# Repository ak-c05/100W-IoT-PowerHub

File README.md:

# 100W IoT Power Hub | ESP32-C3

A custom-engineered, dual-rail Power Delivery (PD) hub featuring hardware-level I2C telemetry, commercial DFM clamshell mechanics, and an asynchronous WebSocket control dashboard. 

---

## Mechanical Engineering (DFM)

The enclosure is architected for a friction-fit prototyping phase, scaling to ultrasonic welding for mass production.
* **Non-Collision Assembly:** Designed with strict vertical U-channels for all I/O ports, eliminating plastic undercuts and allowing seamless top-down Z-axis assembly.
* **Interference Tolerancing:** Utilizes a modeled `0.05mm` press-pull lip-and-groove parting line to achieve a reliable friction fit without failure-prone snap hooks.
* **Kinematic Trapping:** The PCB is cradled by lower bosses and secured by mirrored upper retaining posts featuring a `0.2mm` rattle gap to guarantee closure without crushing the FR4 fiberglass.
* **Captive Actuation:** Features a custom 15mm "long-stem mushroom" plunger mechanism with strict 0.2mm clearance tolerances for the tactile UI switch.

---

## Electrical Architecture

Designed in KiCad 7/8, the motherboard isolates high-power delivery protocols from sensitive RF and logic components.
* **Dual-Rail Telemetry:** Utilizes two Texas Instruments INA219 ICs (I2C) for independent, high-speed monitoring of both the 12V Main and 9V PD lines.
* **Hardware PD Negotiation:** Integrates the autonomous SW3516 buck-boost controller for dedicated Type-C PD 3.0 protocol handshakes, offloading thermal and negotiation logic from the MCU.
* **RF Isolation:** Antenna routing and component placement are optimized to prevent the ESP32-C3's 2.4GHz radio from introducing jitter into the analog-to-digital current sensing pathways.

---

## Embedded Firmware & IoT

The C++ backend operates on a strict, non-blocking deterministic state machine, ensuring network handling never interrupts safety-critical hardware isolation.
* **Asynchronous WebSockets:** The ESP32 hosts a continuous WebSocket tunnel, pushing serialized JSON packets to the frontend only when clients are actively connected, saving CPU cycles.
* **PROGMEM Decoupling:** All HTML, CSS, and JavaScript assets are decoupled into an external `dashboard.h` file and stored in flash memory, preserving SRAM for runtime telemetry.
* **Hardware-Agnostic Graphics:** Drives a 1.3" SH1106 OLED using the U8g2 memory buffer, pushing mathematical frame geometry in single I2C blasts to prevent screen tearing.
* **Zero-Blocking Safety:** The 20-millisecond overcurrent protection polling loop runs independently of the network stack; physical hardware isolation always overrides remote UI commands.

---

## Future Roadmap
* Implementation of `WiFiManager` (Captive Portal) for dynamic AP provisioning, removing hardcoded network credentials from the master branch.

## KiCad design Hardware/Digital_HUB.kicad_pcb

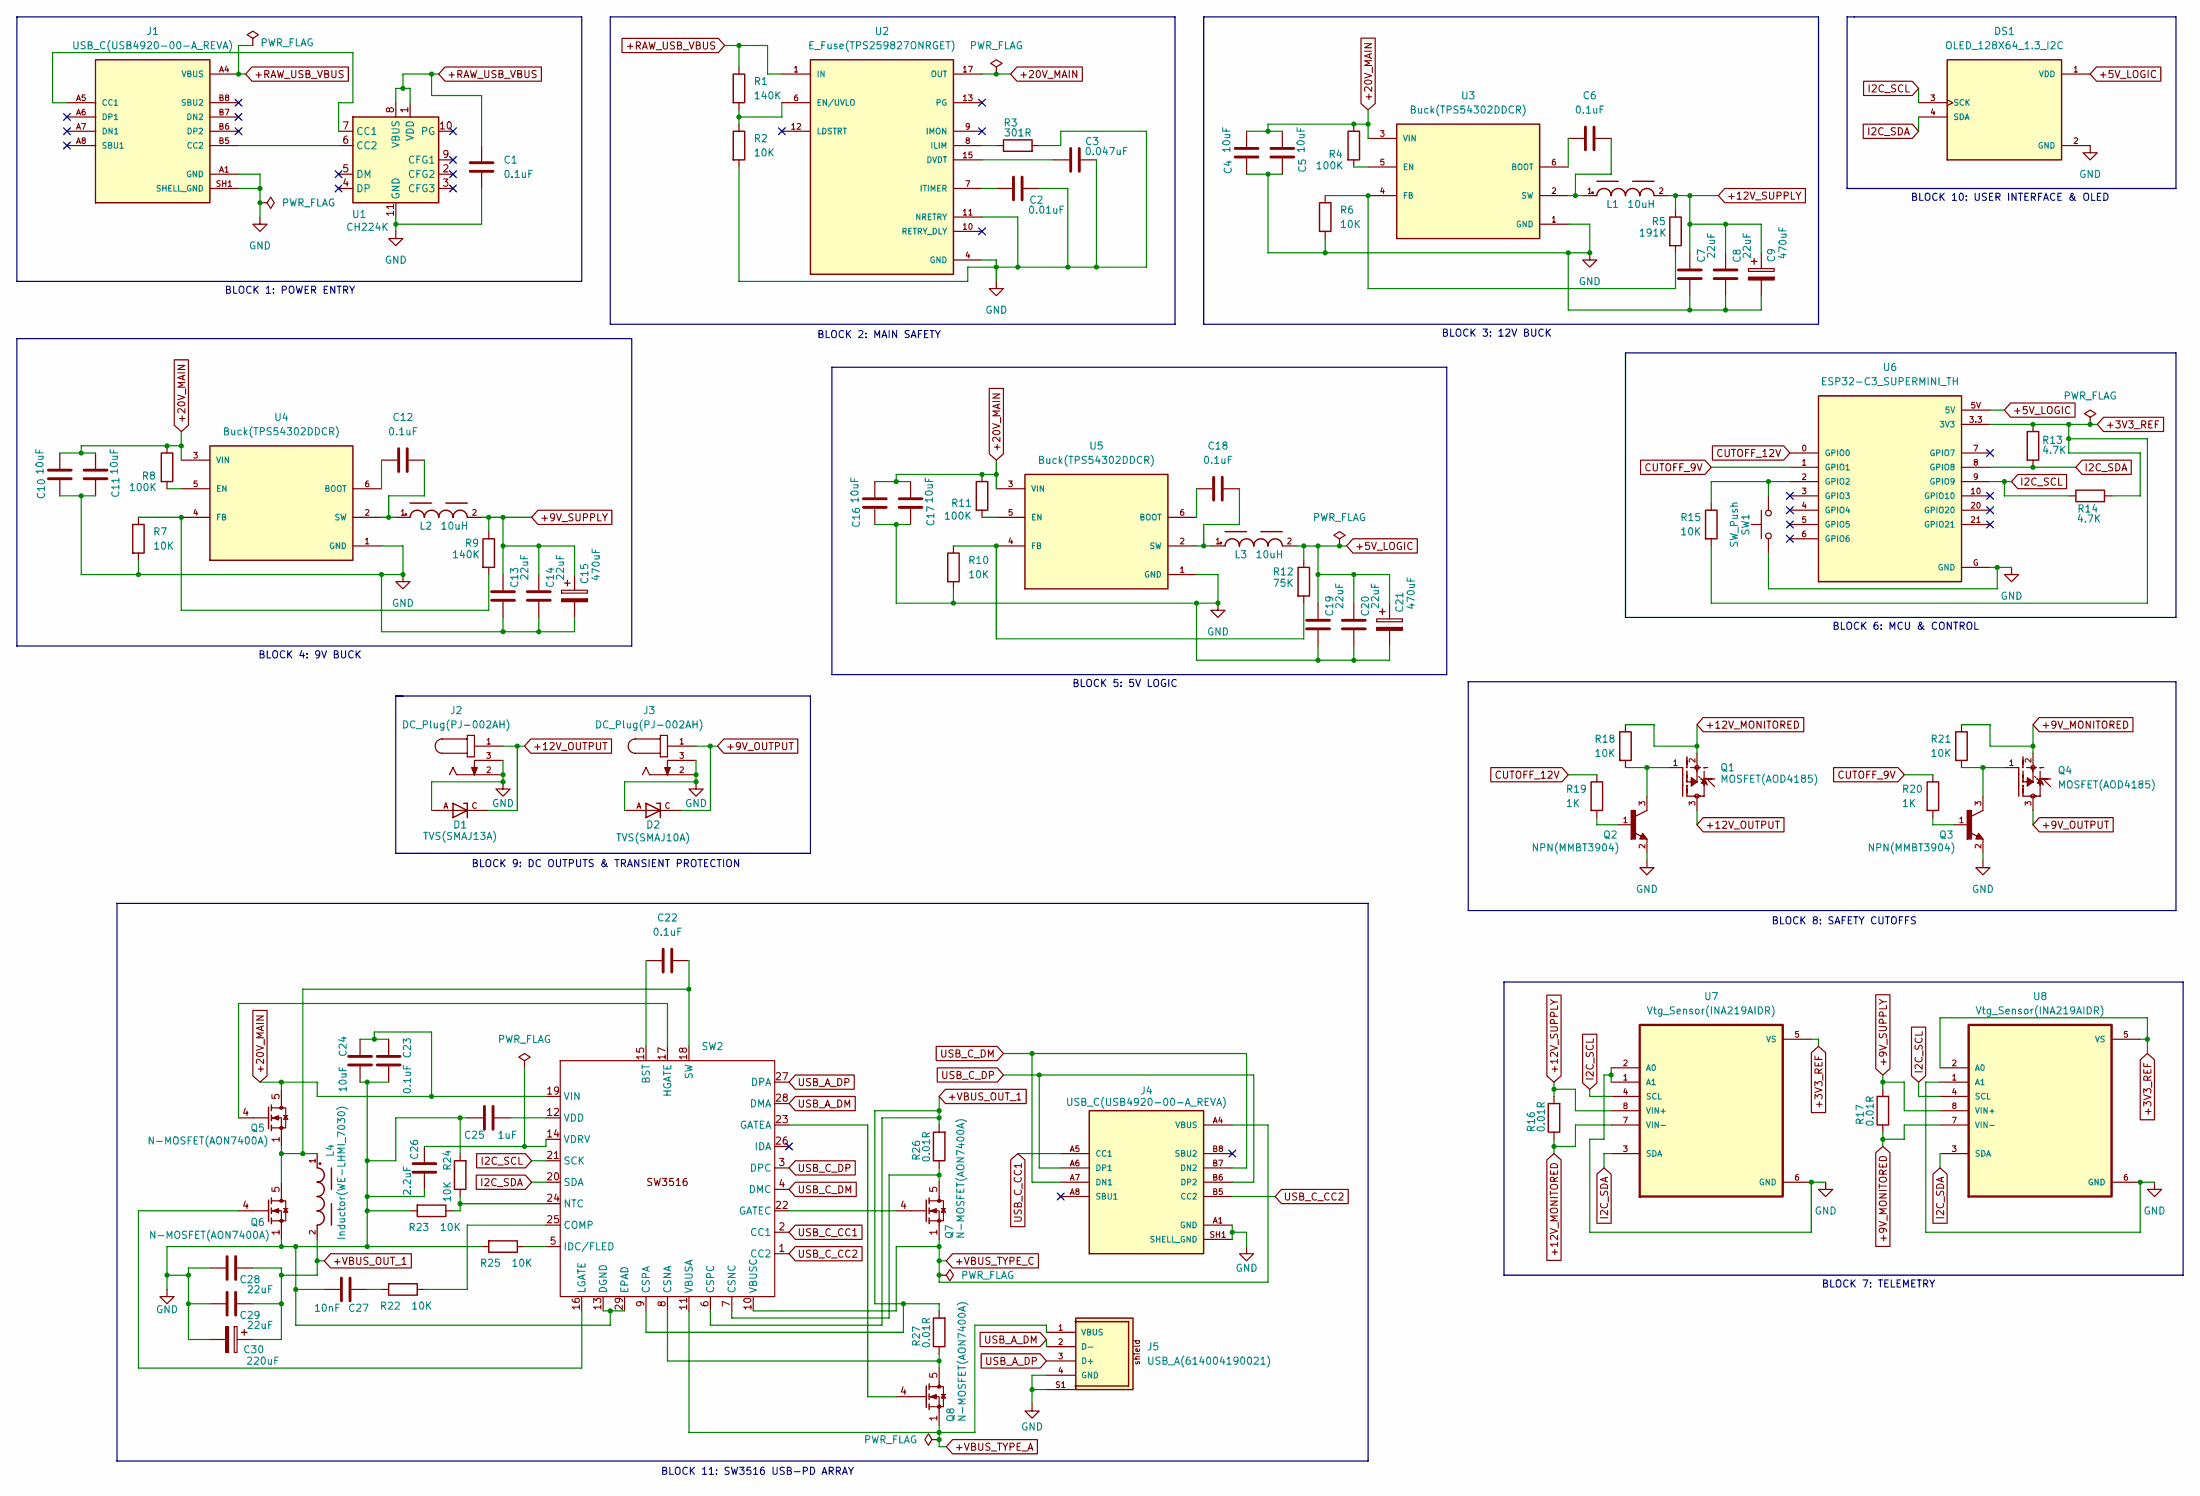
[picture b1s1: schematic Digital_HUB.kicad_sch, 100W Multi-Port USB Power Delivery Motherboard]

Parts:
C1, C6, C12, C18, C22, C23: 0.1uF; C_0603_1608Metric
C2: 0.01uF; C_0603_1608Metric
C3: 0.047uF; C_0603_1608Metric
C4, C5, C10, C11, C16, C17, C24: 10uF; C_0603_1608Metric
C7, C8, C13, C14, C19, C20, C28, C29: 22uF; C_0603_1608Metric
C9, C15, C21: 470uF; CP_Elec_10x10.5
C25: 1uF; C_0603_1608Metric
C26: 2.2uF; C_0603_1608Metric
C27: 10nF; C_0603_1608Metric
C30: 220uF; CP_Elec_10x10.5
D1: TVS(SMAJ13A); TVS13(DIOM4325X250N); PARTREV S2102
D2: TVS(SMAJ10A); TVS10(DIOM4325X250N); PARTREV S2102
DS1: OLED_128X64_1.3_I2C; LCD_OLED_128X64_1.3_I2C; PARTREV NA
J1, J4: USB_C(USB4920-00-A_REVA); USB_C(GCT_USB4920-00-A_REVA); PARTREV A
J2, J3: DC_Plug(PJ-002AH); DC_Plug(CUI_PJ-002AH)
J5: USB_A(614004190021)
L1, L2, L3: 10uH; Inductor(WE-LHMI_7030)
L4: Inductor(WE-LHMI_7030)
Q1, Q4: MOSFET(AOD4185)
Q2, Q3: NPN(MMBT3904); PARTREV 2025-06-30
Q5, Q6, Q7, Q8: N-MOSFET(AON7400A); TRANS_AON7407
R1, R9: 140K; R_0603_1608Metric
R2, R6, R7, R10, R15, R18, R21, R22, R23, R24, R25: 10K; R_0603_1608Metric
R3: 301R; R_0603_1608Metric
R4, R8, R11: 100K; R_0603_1608Metric
R5: 191K; R_0603_1608Metric
R12: 75K; R_0603_1608Metric
R13, R14: 4.7K; R_0603_1608Metric
R16, R17, R26, R27: 0.01R; R_2512_6332Metric
R19, R20: 1K; R_0603_1608Metric
SW1: SW_Push; SW_PUSH_6mm_H5mm
SW2: QFN-28_L4.0-W4.0-P0.40-BL-EP
U1: CH224K; SSOP-10-1EP_3.9x4.9mm_P1mm_EP2.1x3.3mm
U2: E_Fuse(TPS259827ONRGET); E_Fuse(IC_TPS259827ONRGET); PARTREV C
U3, U4, U5: Buck(TPS54302DDCR); Buck(SOT95P280X110-6N); PARTREV A
U6: ESP32-C3_SUPERMINI_TH; MODULE_ESP32-C3_SUPERMINI_TH
U7, U8: Vtg_Sensor(INA219AIDR)

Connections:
+3V3_REF: R13.1, R14.2, R15.2, U6.3.3 (3V3), U7.5 (VS), U8.2 (A0), U8.5 (VS)
+5V_LOGIC: C19.2, C20.2, C21.1, DS1.1 (VDD), L3.2, R12.1, U6.5V
+9V_MONITORED: Q4.2, R17.1, R21.1, U8.7 (VIN-)
+9V_OUTPUT: D2.C, J3.1, Q4.3
+9V_SUPPLY: C13.2, C14.2, C15.1, L2.2, R9.1, R17.2, U8.8 (VIN+)
+12V_MONITORED: Q1.2, R16.1, R18.1, U7.7 (VIN-)
+12V_OUTPUT: D1.C, J2.1, Q1.3
+12V_SUPPLY: C7.2, C8.2, C9.1, L1.2, R5.1, R16.2, U7.8 (VIN+)
+20V_MAIN: C4.2, C5.2, C10.2, C11.2, C16.2, C17.2, C23.1, C24.1, Q5.5 (D), Q5.6 (D), Q5.7 (D), Q5.8 (D), R4.1, R8.1, R11.1, SW2.19 (VIN), U2.17 (OUT), U2.18 (OUT), U2.19 (OUT), U2.20 (OUT), U2.21 (OUT), U2.22 (OUT), U2.23 (OUT), U2.24 (OUT), U3.3 (VIN), U4.3 (VIN), U5.3 (VIN)
+RAW_USB_VBUS: C1.1, J1.A4 (VBUS), J1.A9 (VBUS), J1.B4 (VBUS), J1.B9 (VBUS), R1.1, U1.1 (VDD), U1.8 (VBUS), U2.1 (IN), U2.2 (IN), U2.3 (IN), U2.16 (IN), U2.25 (IN)
+VBUS_OUT_1: C28.2, C29.2, C30.1, L4.2, R26.2, R27.2, SW2.6 (CSPC), SW2.9 (CSPA)
+VBUS_TYPE_A: J5.1 (VBUS), Q8.1 (S), Q8.2 (S), Q8.3 (S), SW2.11 (VBUSA)
+VBUS_TYPE_C: J4.A4 (VBUS), J4.A9 (VBUS), J4.B4 (VBUS), J4.B9 (VBUS), Q7.1 (S), Q7.2 (S), Q7.3 (S), SW2.10 (VBUSC)
CUTOFF_9V: R20.1, U6.1 (GPIO1)
CUTOFF_12V: R19.1, U6.0 (GPIO0)
GND: C1.2, C2.2, C3.2, C4.1, C5.1, C7.1, C8.1, C9.2, C10.1, C11.1, C13.1, C14.1, C15.2, C16.1, C17.1, C19.1, C20.1, C21.2, C23.2, C24.2, C25.1, C26.2, C27.2, C28.1, C29.1, C30.2, D1.A, D2.A, DS1.2 (GND), J1.A1 (GND), J1.A12 (GND), J1.B1 (GND), J1.B12 (GND), J1.SH1 (SHELL_GND), J1.SH2 (SHELL_GND), J1.SH3 (SHELL_GND), J1.SH4 (SHELL_GND), J2.2, J2.3, J3.2, J3.3, J4.A1 (GND), J4.A12 (GND), J4.B1 (GND), J4.B12 (GND), J4.SH1 (SHELL_GND), J4.SH2 (SHELL_GND), J4.SH3 (SHELL_GND), J4.SH4 (SHELL_GND), J5.4 (GND), J5.S1, J5.S2, Q2.2, Q3.2, Q6.1 (S), Q6.2 (S), Q6.3 (S), R2.2, R3.2, R6.2, R7.2, R10.2, R23.2, R24.2, R25.2, SW1.1, SW2.13 (DGND), SW2.29 (EPAD), U1.11 (GND), U2.4 (GND), U2.5 (GND), U2.11 (NRETRY), U2.14 (GND), U2.26 (GND), U3.1 (GND), U4.1 (GND), U5.1 (GND), U6.G (GND), U7.1 (A1), U7.2 (A0), U7.6 (GND), U8.1 (A1), U8.6 (GND)
I2C_SCL: DS1.3 (SCK), R14.1, SW2.21 (SCK), U6.9 (GPIO9), U7.4 (SCL), U8.4 (SCL)
I2C_SDA: DS1.4 (SDA), R13.2, SW2.20 (SDA), U6.8 (GPIO8), U7.3 (SDA), U8.3 (SDA)
unnamed: C27.1, R22.2
unnamed: J1.A5 (CC1), U1.7 (CC1)
unnamed: J1.B5 (CC2), U1.6 (CC2)
unnamed: Q1.1, Q2.3, R18.2
unnamed: Q2.1, R19.2
unnamed: Q3.1, R20.2
unnamed: Q3.3, Q4.1, R21.2
unnamed: Q5.4 (G), SW2.17 (HGATE)
unnamed: Q6.4 (G), SW2.16 (LGATE)
unnamed: Q7.4 (G), SW2.22 (GATEC)
unnamed: Q8.4 (G), SW2.23 (GATEA)
unnamed: C22.1, SW2.15 (BST)
unnamed: R22.1, SW2.25 (COMP)
unnamed: Q8.5 (D), Q8.6 (D), Q8.7 (D), Q8.8 (D), R27.1, SW2.8 (CSNA)
unnamed: Q7.5 (D), Q7.6 (D), Q7.7 (D), Q7.8 (D), R26.1, SW2.7 (CSNC)
unnamed: R25.1, SW2.5 (IDC/FLED)
unnamed: R23.1, R24.1, SW2.24 (NTC)
unnamed: C22.2, L4.1, Q5.1 (S), Q5.2 (S), Q5.3 (S), Q6.5 (D), Q6.6 (D), Q6.7 (D), Q6.8 (D), SW2.18 (SW)
unnamed: C25.2, SW2.12 (VDD)
unnamed: C26.1, SW2.14 (VDRV)
unnamed: C3.1, U2.15 (DVDT)
unnamed: R1.2, R2.1, U2.6 (EN/UVLO)
unnamed: R3.1, U2.8 (ILIM)
unnamed: C2.1, U2.7 (ITIMER)
unnamed: C6.1, U3.6 (BOOT)
unnamed: R4.2, U3.5 (EN)
unnamed: R5.2, R6.1, U3.4 (FB)
unnamed: C6.2, L1.1, U3.2 (SW)
unnamed: C12.1, U4.6 (BOOT)
unnamed: R8.2, U4.5 (EN)
unnamed: R7.1, R9.2, U4.4 (FB)
unnamed: C12.2, L2.1, U4.2 (SW)
unnamed: C18.1, U5.6 (BOOT)
unnamed: R11.2, U5.5 (EN)
unnamed: R10.1, R12.2, U5.4 (FB)
unnamed: C18.2, L3.1, U5.2 (SW)
unnamed: R15.1, SW1.2, U6.2 (GPIO2)
USB_A_DM: J5.2 (D-), SW2.28 (DMA)
USB_A_DP: J5.3 (D+), SW2.27 (DPA)
USB_C_CC1: J4.A5 (CC1), SW2.2 (CC1)
USB_C_CC2: J4.B5 (CC2), SW2.1 (CC2)
USB_C_DM: J4.A7 (DN1), J4.B7 (DN2), SW2.4 (DMC)
USB_C_DP: J4.A6 (DP1), J4.B6 (DP2), SW2.3 (DPC)

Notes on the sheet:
BLOCK 9: DC OUTPUTS & TRANSIENT PROTECTION
BLOCK 8: SAFETY CUTOFFS
BLOCK 1: POWER ENTRY
BLOCK 2: MAIN SAFETY
BLOCK 3: 12V BUCK
BLOCK 11: SW3516 USB-PD ARRAY
BLOCK 10: USER INTERFACE & OLED
BLOCK 7: TELEMETRY
BLOCK 4: 9V BUCK
BLOCK 5: 5V LOGIC
BLOCK 6: MCU & CONTROL

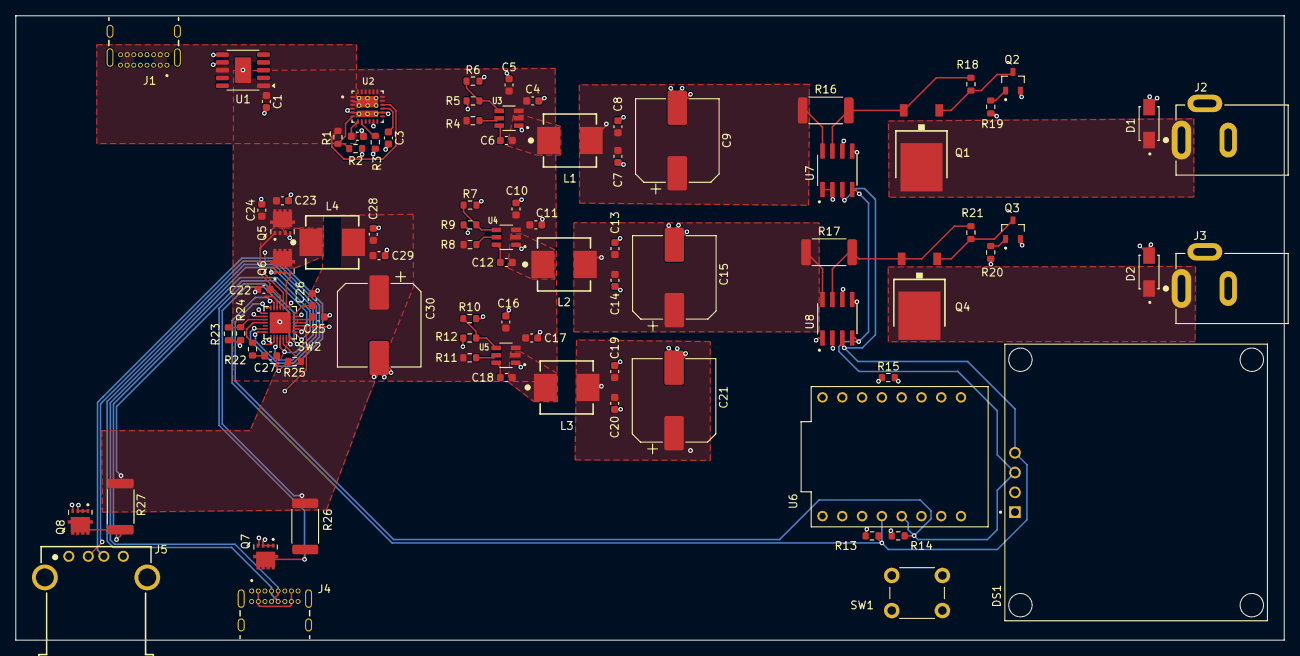
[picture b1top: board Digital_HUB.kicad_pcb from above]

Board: 4 copper layers, 162.8 x 80.1 mm, 87 parts (0 on the bottom side), 61 nets.

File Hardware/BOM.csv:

Reference,Qty,Value,Footprint,MANUFACTURER,MP
"C1,C6,C12,C18,C22,C23",6,0.1uF,Capacitor_SMD:C_0603_1608Metric,Generic,
C2,1,0.01uF,Capacitor_SMD:C_0603_1608Metric,Generic,
C3,1,0.047uF,Capacitor_SMD:C_0603_1608Metric,Generic,
"C4,C5,C10,C11,C16,C17,C24",7,10uF,Capacitor_SMD:C_0603_1608Metric,Generic,
"C7,C8,C13,C14,C19,C20,C28,C29",8,22uF,Capacitor_SMD:C_0603_1608Metric,Generic,
"C9,C15,C21",3,470uF 35V,Capacitor_SMD:CP_Elec_10x10.5,Generic,
C25,1,1uF,Capacitor_SMD:C_0603_1608Metric,Generic,
C26,1,2.2uF,Capacitor_SMD:C_0603_1608Metric,Generic,
C27,1,10nF,Capacitor_SMD:C_0603_1608Metric,Generic,
C30,1,220uF 35V,Capacitor_SMD:CP_Elec_10x10.5,Generic,
D1,1,TVS(SMAJ13A),DigitalHUB:TVS13(DIOM4325X250N),Taiwan Semiconductor,SMAJ13A
D2,1,TVS(SMAJ10A),DigitalHUB:TVS10(DIOM4325X250N),Taiwan Semiconductor,SMAJ10A
DS1,1,OLED_128X64_1.3_I2C,DigitalHUB:LCD_OLED_128X64_1.3_I2C,UNIVERSAL-SOLDER Electronics Ltd,"OLED 128x64 1.3""; I2C"
"J1,J4",2,USB_C(USB4920-00-A_REVA),DigitalHUB:USB_C(GCT_USB4920-00-A_REVA),Global Connector Technology,USB4920-00-A
"J2,J3",2,DC_Plug(PJ-002AH),DigitalHUB:DC_Plug(CUI_PJ-002AH),CUI INC,PJ-002AH
J5,1,USB_A(614004190021),DigitalHUB:USB_A(614004190021),Würth Elektronik,614004190021
"L1,L2,L3,L4",4,10uH,DigitalHUB:Inductor(WE-LHMI_7030),Würth Elektronik,74437346100
"Q1,Q4",2,MOSFET(AOD4185),DigitalHUB:MOSFET(AOD4185),Alpha & Omega,AOD4185
"Q2,Q3",2,NPN(MMBT3904),DigitalHUB:NPN(MMBT3904),Diotec Semiconductor,MMBT3904
"Q5,Q6,Q7,Q8",4,N-MOSFET(AON7400A),DigitalHUB:TRANS_AON7407,Alpha & Omega,AON7400A
"R1,R9",2,140K,Resistor_SMD:R_0603_1608Metric,Generic,
"R2,R6,R7,R10,R15,R18,R21,R22,R23,R24,R25",11,10K,Resistor_SMD:R_0603_1608Metric,Generic,
R3,1,301R,Resistor_SMD:R_0603_1608Metric,Generic,
"R4,R8,R11",3,100K,Resistor_SMD:R_0603_1608Metric,Generic,
R5,1,191K,Resistor_SMD:R_0603_1608Metric,Generic,
R12,1,75K,Resistor_SMD:R_0603_1608Metric,Generic,
"R13,R14",2,4.7K,Resistor_SMD:R_0603_1608Metric,Generic,
"R16,R17,R26,R27",4,0.01R 2W 1%,Resistor_SMD:R_2512_6332Metric,Generic,
"R19,R20",2,1K,Resistor_SMD:R_0603_1608Metric,Generic,
SW1,1,SW_Push,Button_Switch_THT:SW_PUSH_6mm_H5mm,Generic,
SW2,1,SW3516,DigitalHUB:QFN-28_L4.0-W4.0-P0.40-BL-EP,Ismartware,SW3516
U1,1,CH224K,Package_SO:SSOP-10-1EP_3.9x4.9mm_P1mm_EP2.1x3.3mm,WCH,CH224K
U2,1,E_Fuse(TPS259827ONRGET),DigitalHUB:E_Fuse(IC_TPS259827ONRGET),Texas Instruments,TPS259827ONRGET
"U3,U4,U5",3,Buck(TPS54302DDCR),DigitalHUB:Buck(SOT95P280X110-6N),Texas Instruments,TPS54302DDCR
U6,1,ESP32-C3_SUPERMINI_TH,DigitalHUB:MODULE_ESP32-C3_SUPERMINI_TH,Espressif Systems,ESP32-C3 SuperMini_TH
"U7,U8",2,Vtg_Sensor(INA219AIDR),DigitalHUB:Vtg_Sensor(INA219AIDR),Texas Instruments,INA219AIDR
